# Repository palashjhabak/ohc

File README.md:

Open Home Control
=================

Open Home Control (OHC) is an **open source home automation system**
providing a framework for building up a bigger network of sensors and
actuators that all work together. It consists of several completely
developed hardware devices you can build up yourself and the software
running on those devices.

This project **concentrates on the hardware devices** and their software
(firmware), not on end user interfaces for control tasks like web
interfaces or smartphone apps. Nonetheless this system is designed to be
easily integrated in such systems.

For more information, visit the website at
http://www.open-home-control.com.

License Information Hardware Files
----------------------------------

All **hardware** files (schematics and layout) are stored under the
"hardware" subdirectory and are copyright (c) 2013 Uwe Freese, licensed
under the Creative Commons Attribution-ShareAlike 3.0 Unported:
(CC BY-SA 3.0): http://creativecommons.org/licenses/by-sa/3.0/deed.en.

License Information Software
----------------------------

All files not in the hardware subdirectory belong to the software (device
firmware or control software).

The Open Home Control **software** is free software: you can redistribute
it and/or modify it under the terms of the GNU General Public License as
published by the Free Software Foundation, either version 3 of the
License, or (at your option) any later version.

Open Home Control is distributed in the hope that it will be useful, but
WITHOUT ANY WARRANTY; without even the implied warranty of
MERCHANTABILITY or FITNESS FOR A PARTICULAR PURPOSE. See the GNU General
Public License for more details.

You should have received a copy of the GNU General Public License along
with Open Home Control. If not, see <http://www.gnu.org/licenses/>.

License Information Logo
------------------------

The Open Home Control logo ("House") and logotype, also used in the
hardware layouts, are copyrighted (c) by 2013 by Uwe Freese.

The logo and logotype may be used on hardware (boards or devices) or
description of those only for private purposes for devices included in
the project repository and which are therefore available to the public.
For derived or modified versions, devices not existing in the repository,
completely different products or for commercial boards or devices or to
describe them, the logo must not be used without explicit permission from
Uwe Freese.

For more information on using the logo or logotype outside the hardware
layouts, please read the legal info on the website
http://www.open-home-control.com.

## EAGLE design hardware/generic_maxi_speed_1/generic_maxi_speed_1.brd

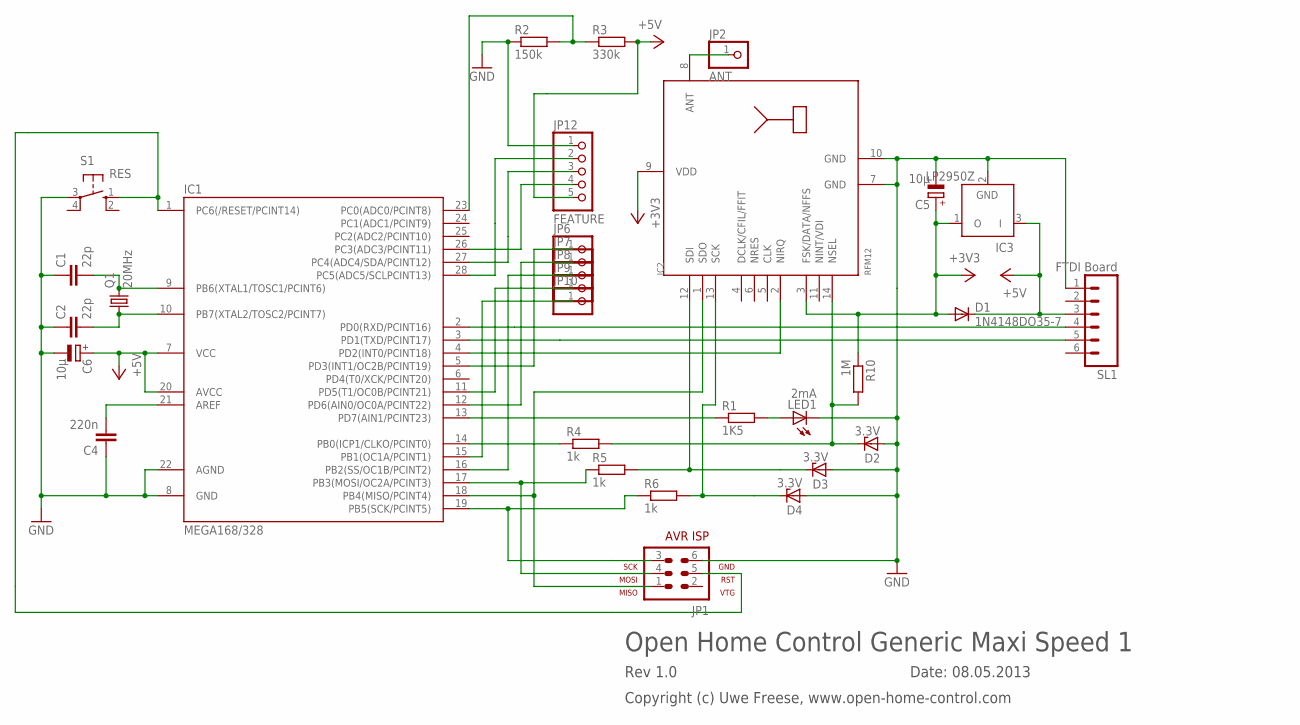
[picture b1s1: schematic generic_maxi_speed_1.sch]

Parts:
C1, C2: 22p; C025-024X044
C4: 220n; C025-030X050
C5, C6: 10µ; E1,8-4
D1: 1N4148DO35-7; DO35-7
D2, D3, D4: 3.3V; ZDIO-5
IC1: MEGA168/328; DIL28-3
IC2: RFM12; RFM
IC3: LP2950Z; TO92
JP1: AVR-ISP-6
JP2: ANT; 1X01
JP6, JP7, JP8, JP9, JP10: PINHD-1X1; 1X01
JP12: FEATURE; 1X05
LED1: 2mA; LED3MM
Q1: 20MHz; HC49/S
R1: 1K5; 0207/7
R2: 150k; 0207/7
R3: 330k; 0207/7
R4, R5, R6: 1k; 0207/7
R10: 1M; 0207/7
S1: RES; B3F-10XX
SL1: FTDI Board; 06P

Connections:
+3V3: C5.+, D1.A, IC2.3 (FSK/DATA/NFFS), IC2.9 (VDD), IC3.1 (O), R10.1
+5V: C6.+, D1.C, IC1.7 (VCC), IC1.20 (AVCC), IC3.3 (I), JP12.5, R3.2, SL1.3
GND: C1.1, C2.1, C4.1, C5.-, C6.-, D2.A, D3.A, D4.A, IC1.8 (GND), IC1.22 (AGND), IC2.7 (GND), IC2.10 (GND), IC3.2 (GND), JP1.6, JP12.1, LED1.K (C), R2.1, S1.3, SL1.1
unnamed: C1.2, IC1.9 (PB6(XTAL1/TOSC1/PCINT6)), Q1.2
unnamed: C2.2, IC1.10 (PB7(XTAL2/TOSC2/PCINT7)), Q1.1
unnamed: IC1.17 (PB3(MOSI/OC2A/PCINT3)), JP1.4, R5.1
unnamed: IC1.18 (PB4(MISO/PCINT4)), IC2.1 (SDO), JP1.1
unnamed: D4.C, IC2.13 (SCK), R6.2
unnamed: IC1.28 (PC5(ADC5/SCLPCINT13)), JP12.2
unnamed: IC1.19 (PB5(SCK/PCINT5)), JP1.3, R6.1
unnamed: IC1.1 (PC6(/RESET/PCINT14)), JP1.5, S1.1 (S)
unnamed: IC1.3 (PD1(TXD/PCINT17)), SL1.5
unnamed: IC1.2 (PD0(RXD/PCINT16)), SL1.4
unnamed: IC1.27 (PC4(ADC4/SDA/PCINT12)), JP12.3
unnamed: LED1.A, R1.2
unnamed: IC1.26 (PC3(ADC3/PCINT11)), JP12.4
unnamed: IC1.4 (PD2(INT0/PCINT18)), IC2.2 (NIRQ)
unnamed: D3.C, IC2.12 (SDI), R5.2
unnamed: IC1.5 (PD3(INT1/OC2B/PCINT19)), JP6.1
unnamed: IC1.23 (PC0(ADC0/PCINT8)), R2.2, R3.1
unnamed: IC1.11 (PD5(T1/OC0B/PCINT21)), JP9.1
unnamed: IC1.12 (PD6(AIN0/OC0A/PCINT22)), JP7.1
unnamed: IC1.13 (PD7(AIN1/PCINT23)), R1.1
unnamed: IC1.15 (PB1(OC1A/PCINT1)), JP10.1
unnamed: IC1.16 (PB2(SS/OC1B/PCINT2)), JP8.1
unnamed: C4.2, IC1.21 (AREF)
unnamed: IC2.8 (ANT), JP2.1
unnamed: IC1.14 (PB0(ICP1/CLKO/PCINT0)), R4.1
unnamed: D2.C, IC2.14 (NSEL), R4.2, R10.2

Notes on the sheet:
Open Home Control Generic Maxi Speed 1
Date: 08.05.2013
Rev 1.0
Copyright (c) Uwe Freese, www.open-home-control.com

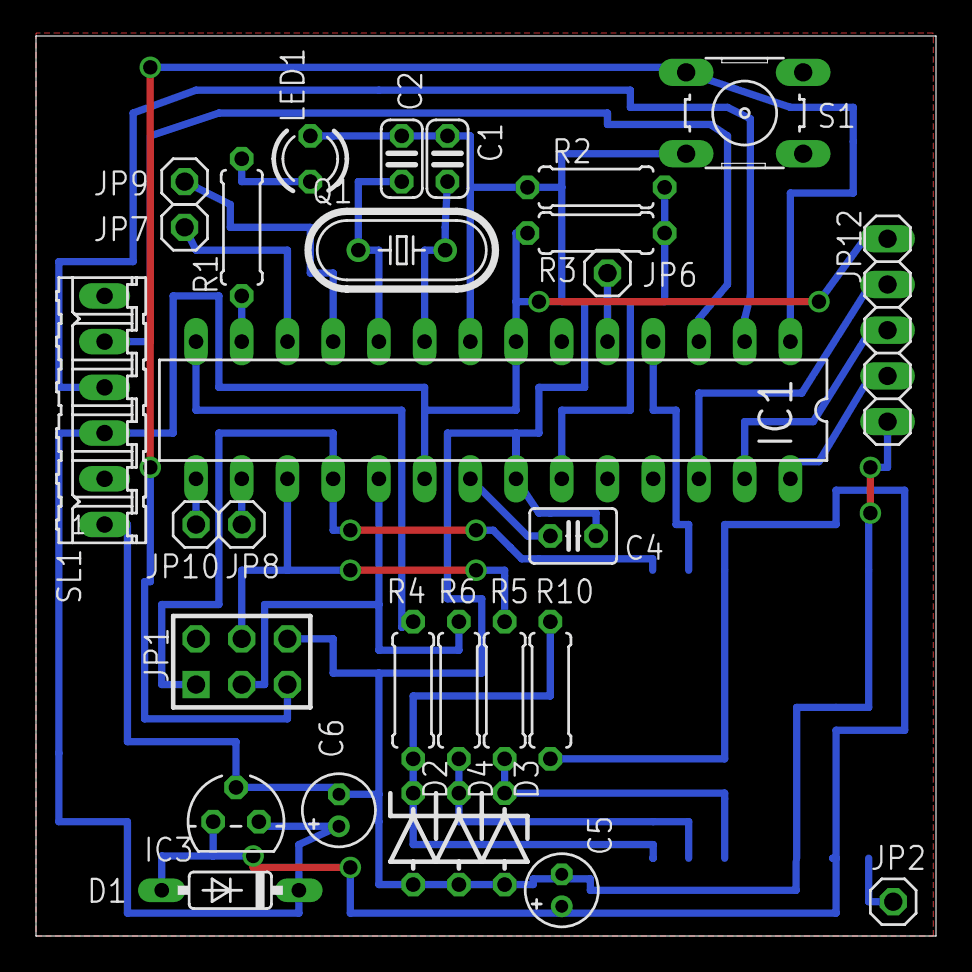
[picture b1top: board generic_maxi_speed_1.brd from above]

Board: 2 copper layers, 50.0 x 50.0 mm, 31 parts (1 on the bottom side), 29 nets.

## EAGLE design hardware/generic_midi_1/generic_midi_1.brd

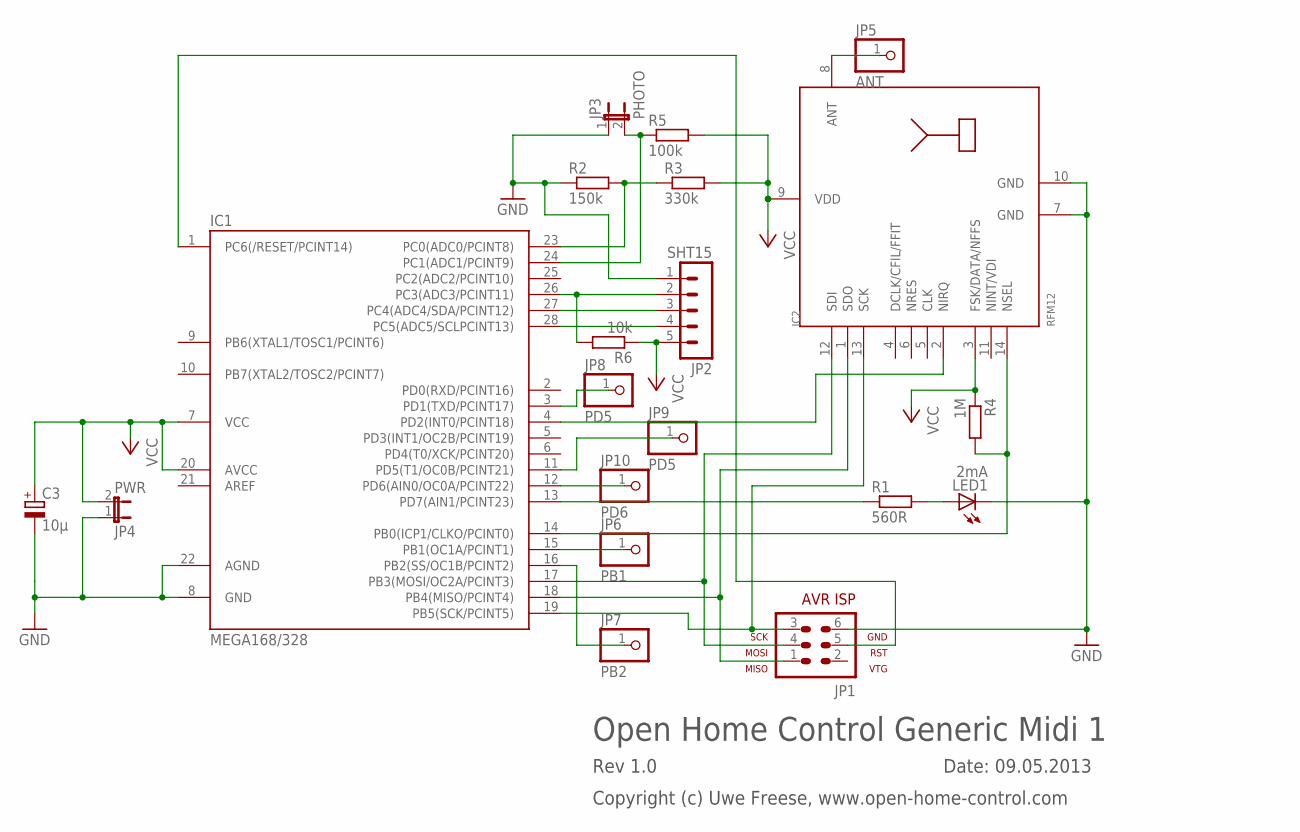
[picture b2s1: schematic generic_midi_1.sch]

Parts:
C3: 10µ; E1,8-4
IC1: MEGA168/328; DIL28-3
IC2: RFM12; RFM
JP1: AVR-ISP-6
JP2: SHT15; MA05-1
JP3: PHOTO; JP1
JP4: PWR; JP1
JP5: ANT; 1X01
JP6: PB1; 1X01
JP7: PB2; 1X01
JP8, JP9: PD5; 1X01
JP10: PD6; 1X01
LED1: 2mA; LED3MM
R1: 560R; 0207/7
R2: 150k; 0207/7
R3: 330k; 0207/7
R4: 1M; 0207/7
R5: 100k; 0207/7
R6: 10k; 0207/7

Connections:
GND: C3.-, IC1.8 (GND), IC1.22 (AGND), IC2.7 (GND), IC2.10 (GND), JP1.6, JP2.1, JP3.1, JP4.1, LED1.K (C), R2.1
unnamed: IC1.24 (PC1(ADC1/PCINT9)), JP3.2, R5.1
unnamed: IC1.17 (PB3(MOSI/OC2A/PCINT3)), IC2.12 (SDI), JP1.4
unnamed: IC1.18 (PB4(MISO/PCINT4)), IC2.1 (SDO), JP1.1
unnamed: IC1.19 (PB5(SCK/PCINT5)), IC2.13 (SCK), JP1.3
unnamed: IC1.13 (PD7(AIN1/PCINT23)), R1.1
unnamed: IC1.27 (PC4(ADC4/SDA/PCINT12)), JP2.3
unnamed: IC1.1 (PC6(/RESET/PCINT14)), JP1.5
unnamed: IC1.28 (PC5(ADC5/SCLPCINT13)), JP2.4
unnamed: IC1.26 (PC3(ADC3/PCINT11)), JP2.2, R6.2
unnamed: IC2.8 (ANT), JP5.1
unnamed: LED1.A, R1.2
unnamed: IC1.14 (PB0(ICP1/CLKO/PCINT0)), IC2.14 (NSEL), R4.2
unnamed: IC1.11 (PD5(T1/OC0B/PCINT21)), JP9.1
unnamed: IC1.4 (PD2(INT0/PCINT18)), IC2.2 (NIRQ)
unnamed: IC1.12 (PD6(AIN0/OC0A/PCINT22)), JP10.1
unnamed: IC1.15 (PB1(OC1A/PCINT1)), JP6.1
unnamed: IC1.23 (PC0(ADC0/PCINT8)), R2.2, R3.1
unnamed: IC1.16 (PB2(SS/OC1B/PCINT2)), JP7.1
unnamed: IC1.3 (PD1(TXD/PCINT17)), JP8.1
VCC: C3.+, IC1.7 (VCC), IC1.20 (AVCC), IC2.3 (FSK/DATA/NFFS), IC2.9 (VDD), JP2.5, JP4.2, R3.2, R4.1, R5.2, R6.1

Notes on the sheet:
Open Home Control Generic Midi 1
Date: 09.05.2013
Rev 1.0
Copyright (c) Uwe Freese, www.open-home-control.com

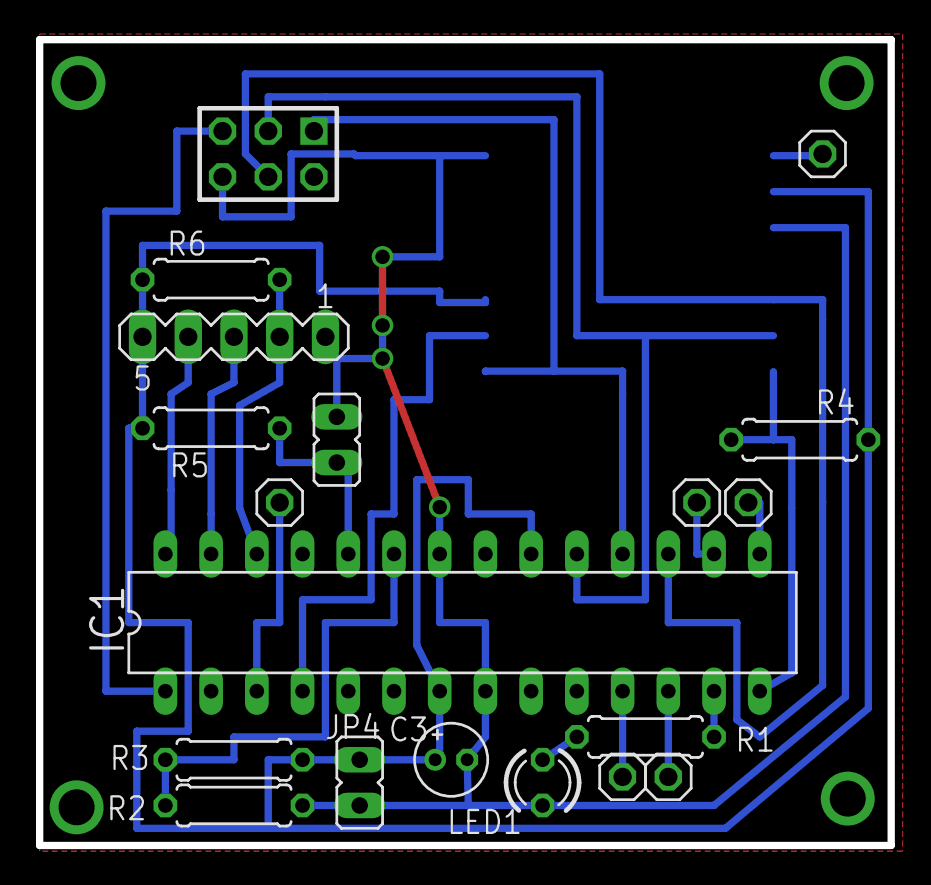
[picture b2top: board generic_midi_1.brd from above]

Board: 2 copper layers, 47.3 x 44.8 mm, 20 parts (1 on the bottom side), 21 nets.

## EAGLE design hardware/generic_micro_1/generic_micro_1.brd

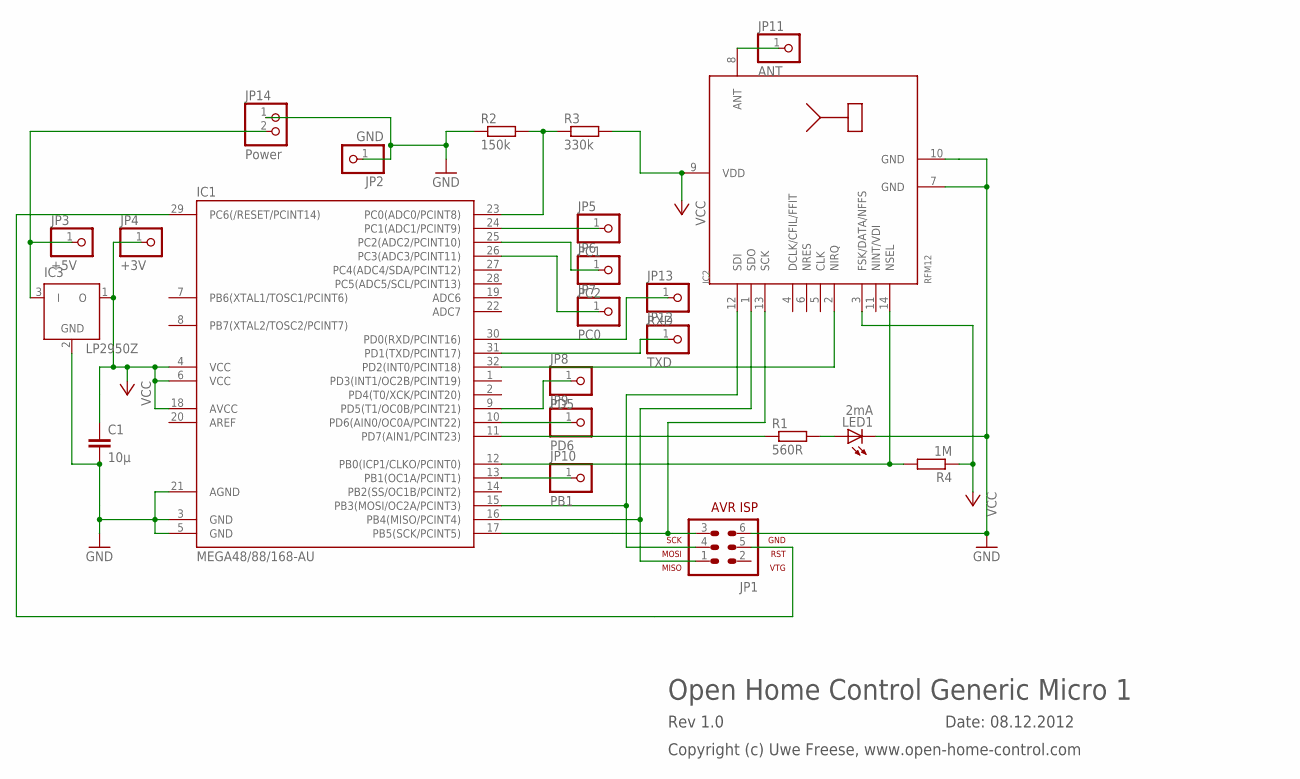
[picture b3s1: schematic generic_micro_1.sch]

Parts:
C1: 10µ; C0805
IC1: MEGA48/88/168-AU; TQFP32-08
IC2: RFM12; RFM
IC3: LP2950Z; TO92
JP1: AVR-ISP-6
JP2: GND; 1X01
JP3: +5V; 1X01
JP4: +3V; 1X01
JP5: PC1; 1X01
JP6: PC2; 1X01
JP7: PC0; 1X01
JP8: PD5; 1X01
JP9: PD6; 1X01
JP10: PB1; 1X01
JP11: ANT; 1X01
JP12: TXD; 1X01
JP13: RXD; 1X01
JP14: Power; 1X02
LED1: 2mA; LED3MM
R1: 560R; R0603
R2: 150k; R0603
R3: 330k; R0603
R4: 1M; R0603

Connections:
GND: C1.2, IC1.3 (GND), IC1.5 (GND), IC1.21 (AGND), IC2.7 (GND), IC2.10 (GND), IC3.2 (GND), JP1.6, JP2.1, JP14.1, LED1.K (C), R2.1
unnamed: IC1.26 (PC3(ADC3/PCINT11)), JP7.1
unnamed: IC1.24 (PC1(ADC1/PCINT9)), JP5.1
unnamed: IC1.15 (PB3(MOSI/OC2A/PCINT3)), IC2.12 (SDI), JP1.4
unnamed: IC1.16 (PB4(MISO/PCINT4)), IC2.1 (SDO), JP1.1
unnamed: IC1.17 (PB5(SCK/PCINT5)), IC2.13 (SCK), JP1.3
unnamed: IC1.11 (PD7(AIN1/PCINT23)), R1.1
unnamed: IC1.25 (PC2(ADC2/PCINT10)), JP6.1
unnamed: IC1.29 (PC6(/RESET/PCINT14)), JP1.5
unnamed: IC1.10 (PD6(AIN0/OC0A/PCINT22)), JP9.1
unnamed: IC1.9 (PD5(T1/OC0B/PCINT21)), JP8.1
unnamed: IC1.13 (PB1(OC1A/PCINT1)), JP10.1
unnamed: LED1.A, R1.2
unnamed: IC1.12 (PB0(ICP1/CLKO/PCINT0)), IC2.14 (NSEL), R4.2
unnamed: IC1.23 (PC0(ADC0/PCINT8)), R2.2, R3.1
unnamed: IC1.32 (PD2(INT0/PCINT18)), IC2.2 (NIRQ)
unnamed: IC2.8 (ANT), JP11.1
unnamed: IC3.3 (I), JP3.1, JP14.2
unnamed: IC1.31 (PD1(TXD/PCINT17)), JP12.1
unnamed: IC1.30 (PD0(RXD/PCINT16)), JP13.1
VCC: C1.1, IC1.4 (VCC), IC1.6 (VCC), IC1.18 (AVCC), IC2.3 (FSK/DATA/NFFS), IC2.9 (VDD), IC3.1 (O), JP4.1, R3.2, R4.1

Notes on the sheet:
Open Home Control Generic Micro 1
Date: 08.12.2012
Rev 1.0
Copyright (c) Uwe Freese, www.open-home-control.com

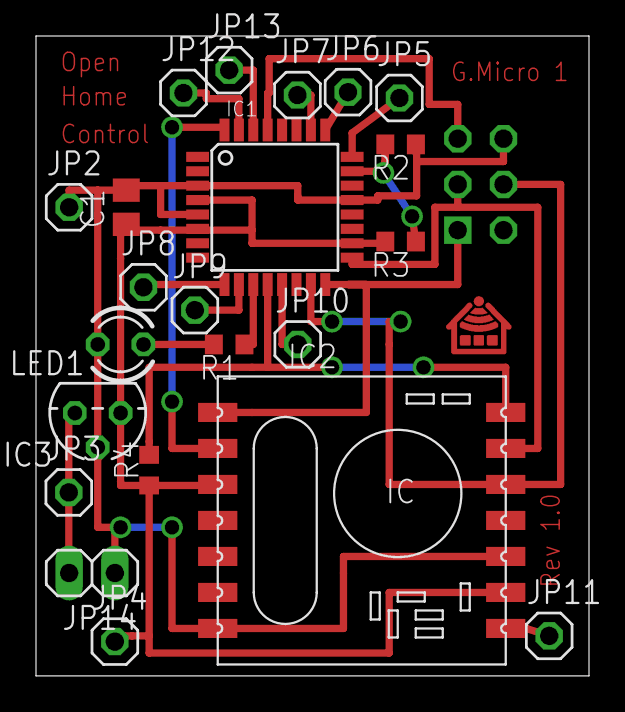
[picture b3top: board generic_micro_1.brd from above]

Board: 2 copper layers, 30.7 x 35.5 mm, 23 parts (1 on the bottom side), 21 nets.

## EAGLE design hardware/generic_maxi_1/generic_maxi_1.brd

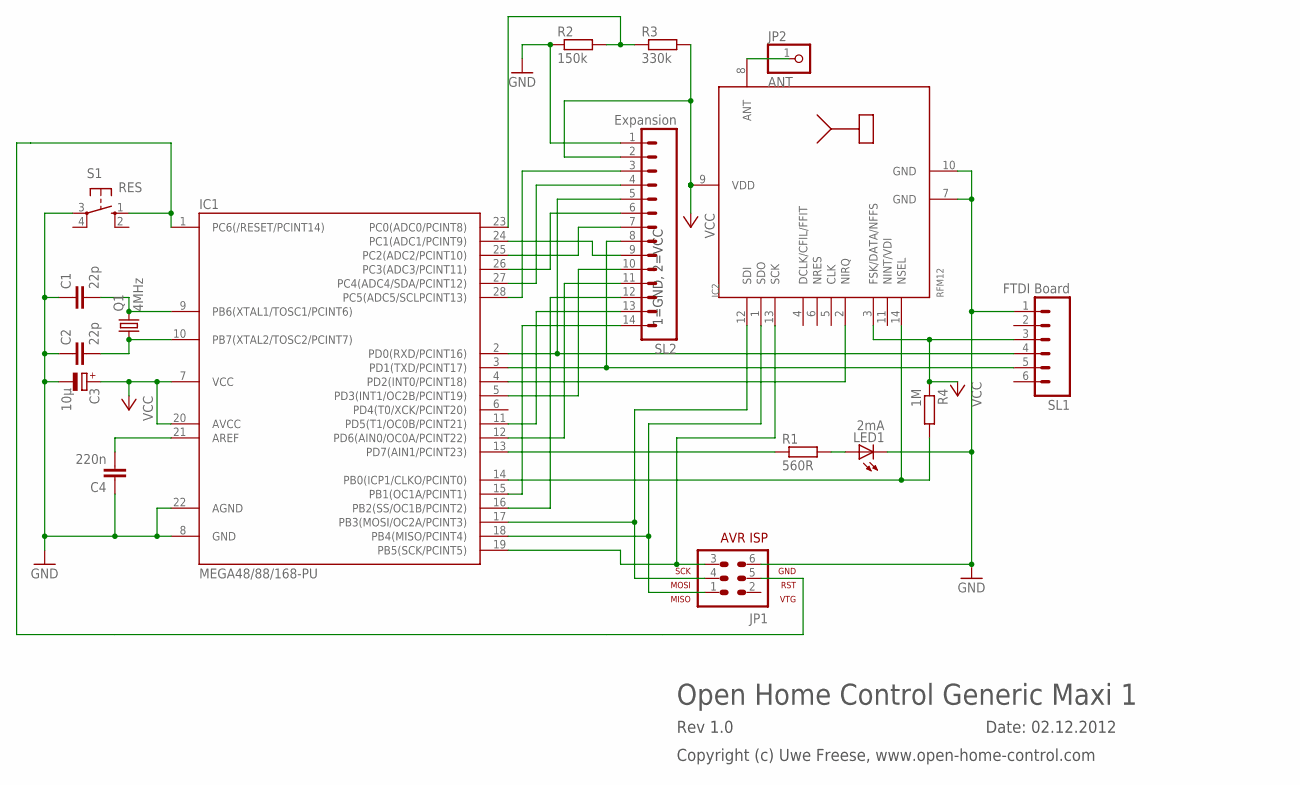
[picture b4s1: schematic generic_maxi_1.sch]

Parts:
C1, C2: 22p; C025-024X044
C3: 10µ; E1,8-4
C4: 220n; C025-030X050
IC1: MEGA48/88/168-PU; DIL28-3
IC2: RFM12; RFM
JP1: AVR-ISP-6
JP2: ANT; 1X01
LED1: 2mA; LED3MM
Q1: 4MHz; HC49/S
R1: 560R; 0207/7
R2: 150k; 0207/7
R3: 330k; 0207/7
R4: 1M; 0207/7
S1: RES; B3F-10XX
SL1: FTDI Board; 06P
SL2: Expansion; 14P

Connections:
GND: C1.1, C2.1, C3.-, C4.1, IC1.8 (GND), IC1.22 (AGND), IC2.7 (GND), IC2.10 (GND), JP1.6, LED1.K (C), R2.1, S1.3, SL1.1, SL2.1
unnamed: C1.2, IC1.9 (PB6(XTAL1/TOSC1/PCINT6)), Q1.2
unnamed: C2.2, IC1.10 (PB7(XTAL2/TOSC2/PCINT7)), Q1.1
unnamed: IC1.17 (PB3(MOSI/OC2A/PCINT3)), IC2.12 (SDI), JP1.4
unnamed: IC1.18 (PB4(MISO/PCINT4)), IC2.1 (SDO), JP1.1
unnamed: IC1.19 (PB5(SCK/PCINT5)), IC2.13 (SCK), JP1.3
unnamed: IC1.27 (PC4(ADC4/SDA/PCINT12)), SL2.4
unnamed: IC1.28 (PC5(ADC5/SCLPCINT13)), SL2.3
unnamed: IC1.1 (PC6(/RESET/PCINT14)), JP1.5, S1.1 (S)
unnamed: IC1.3 (PD1(TXD/PCINT17)), SL1.5, SL2.8
unnamed: IC1.2 (PD0(RXD/PCINT16)), SL1.4, SL2.5
unnamed: IC1.24 (PC1(ADC1/PCINT9)), SL2.9
unnamed: LED1.A, R1.2
unnamed: IC1.14 (PB0(ICP1/CLKO/PCINT0)), IC2.14 (NSEL), R4.2
unnamed: IC1.25 (PC2(ADC2/PCINT10)), SL2.7
unnamed: IC1.4 (PD2(INT0/PCINT18)), IC2.2 (NIRQ)
unnamed: IC1.26 (PC3(ADC3/PCINT11)), SL2.6
unnamed: IC1.5 (PD3(INT1/OC2B/PCINT19)), SL2.10
unnamed: IC1.23 (PC0(ADC0/PCINT8)), R2.2, R3.1
unnamed: IC1.11 (PD5(T1/OC0B/PCINT21)), SL2.13
unnamed: IC1.12 (PD6(AIN0/OC0A/PCINT22)), SL2.11
unnamed: IC1.13 (PD7(AIN1/PCINT23)), R1.1
unnamed: IC1.15 (PB1(OC1A/PCINT1)), SL2.14
unnamed: IC1.16 (PB2(SS/OC1B/PCINT2)), SL2.12
unnamed: C4.2, IC1.21 (AREF)
unnamed: IC2.8 (ANT), JP2.1
VCC: C3.+, IC1.7 (VCC), IC1.20 (AVCC), IC2.3 (FSK/DATA/NFFS), IC2.9 (VDD), R3.2, R4.1, SL1.3, SL2.2

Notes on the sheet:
1=GND, 2=VCC
Open Home Control Generic Maxi 1
Date: 02.12.2012
Rev 1.0
Copyright (c) Uwe Freese, www.open-home-control.com

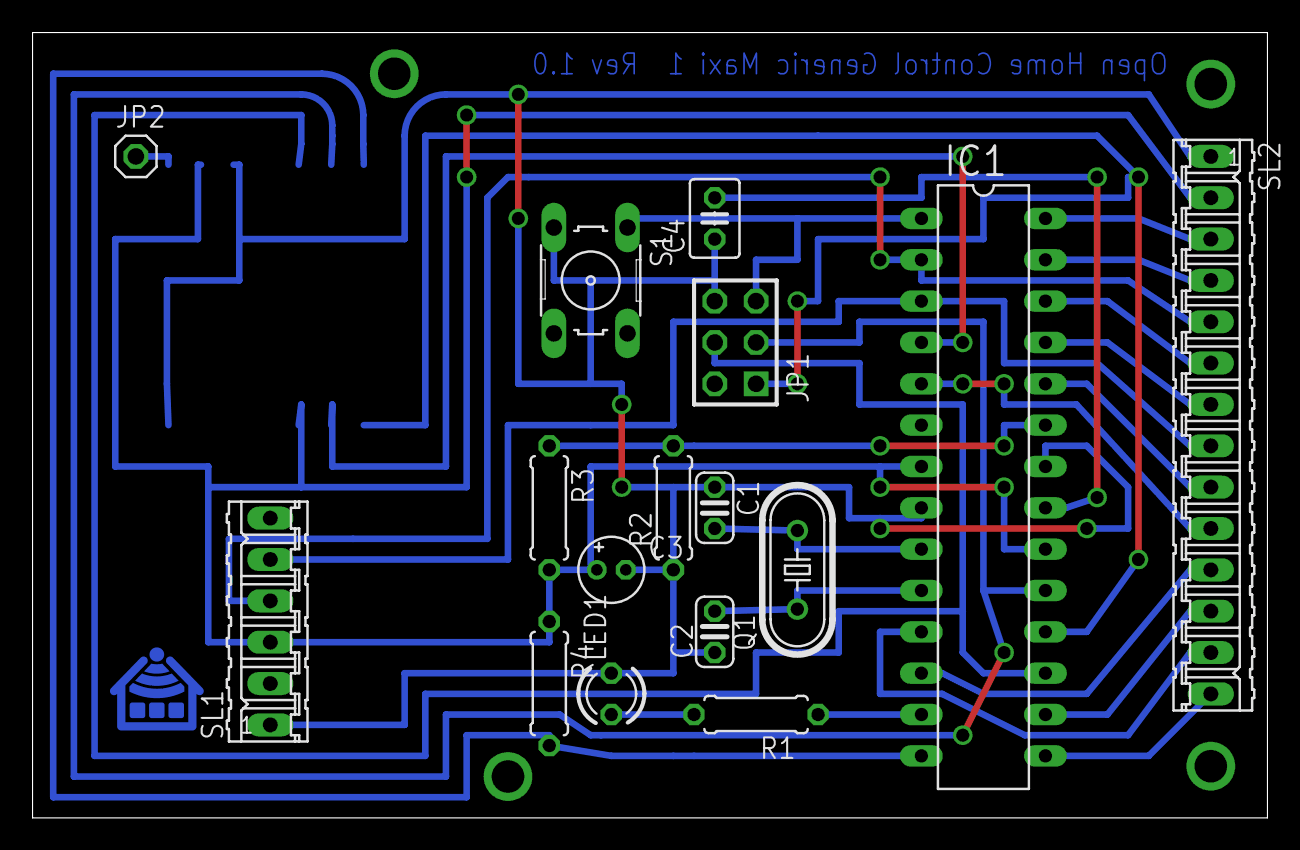
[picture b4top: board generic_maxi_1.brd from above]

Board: 2 copper layers, 75.9 x 48.2 mm, 17 parts (1 on the bottom side), 27 nets.

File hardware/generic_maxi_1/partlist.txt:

Partlist

Exported from generic_maxi_1.sch at 05.11.2012 21:27:49

EAGLE Version 6.2.0 Copyright (c) 1988-2012 CadSoft

Assembly variant: 

Part     Value            Device           Package      Library       Sheet

C1       22p              C-EU025-024X044  C025-024X044 rcl           1
C2       22p              C-EU025-024X044  C025-024X044 rcl           1
C3       10µ              CPOL-EUE1.8-4    E1,8-4       rcl           1
C4       220n             C-EU025-030X050  C025-030X050 rcl           1
IC1      MEGA48/88/168-PU MEGA48/88/168-PU DIL28-3      avr-5-4.16    1
IC2      RFM12            RFM12            RFM          hopeRF        1
JP1      AVR-ISP-6        AVR-ISP-6        AVR-ISP-6    avr-5-4.16    1
JP2      ANT              PINHD-1X1        1X01         pinhead       1
LED1     2mA              LED3MM           LED3MM       led           1
Q1       4MHz             CRYSTALHC49S     HC49/S       crystal       1
R1       750R             R-EU_0207/7      0207/7       rcl           1
R2       150k             R-EU_0207/7      0207/7       rcl           1
R3       330k             R-EU_0207/7      0207/7       rcl           1
R4       1M               R-EU_0207/7      0207/7       rcl           1
S1       RES              10-XX            B3F-10XX     switch-omron  1
SL1      FTDI Board       M06              06P          con-amp-quick 1
SL2      Expansion        M14              14P          con-amp-quick 1

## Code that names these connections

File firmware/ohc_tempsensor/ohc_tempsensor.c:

/*
* This file is part of Open Home Control, http://www.open-home-control.com.
* Copyright (c) 2013 Uwe Freese
*
* Open Home Control is free software: you can redistribute it and/or modify
* it under the terms of the GNU General Public License as published by the
* Free Software Foundation, either version 3 of the License, or (at your
* option) any later version.
*
* Open Home Control is distributed in the hope that it will be useful, but
* WITHOUT ANY WARRANTY; without even the implied warranty of
* MERCHANTABILITY or FITNESS FOR A PARTICULAR PURPOSE. See the GNU General
* Public License for more details.
*
* You should have received a copy of the GNU General Public License along
* with Open Home Control. If not, see <http://www.gnu.org/licenses/>.
*/

#include <avr/io.h>
#include <avr/interrupt.h>
#include <util/delay.h>
#include <string.h>
#include <avr/wdt.h>
#include <avr/sleep.h>
#include <avr/eeprom.h>

#include "rfm12.h"
#include "uart.h"

// switch on debugging by UART
//#define UART_DEBUG

// switch on voltage check of battery on PC0 (ADC0)
#define VBAT_SENSOR

// switch on SHT15 temperature / humidity sensor on PC2 + PC3
#define TEMP_SENS

// switch on light sensor on PC1 (ADC1)
#define LIGHT_SENS

#ifdef TEMP_SENS
	#include "sht11.h"
#endif

#include "../src_common/aes256.h"
#include "util.h"

#define AVERAGE_COUNT 4 // Average over how many values before sending over RFM12?

#define EEPROM_POS_DEVICE_ID 8
#define EEPROM_POS_PACKET_COUNTER 9
#define EEPROM_POS_AES_KEY 32

// How often should the packetcounter_base be increased and written to EEPROM?
// This should be 2^32 (which is the maximum transmitted packet counter) /
// 100.000 (which is the maximum amount of possible EEPROM write cycles) or more.
// Therefore 100 is a good value.
#define PACKET_COUNTER_WRITE_CYCLE 100

uint32_t packetcounter = 0;

void printbytearray(uint8_t * b, uint8_t len)
{
	uint8_t i;
	
	for (i = 0; i < len; i++)
	{
		UART_PUTF("%02x ", b[i]);
	}
	
	UART_PUTS ("\r\n");
}

void rfm12_sendbuf(void)
{
	#ifdef UART_DEBUG
	UART_PUTS("Before encryption: ");
	printbytearray(bufx, 16);
	#endif

	uint8_t aes_byte_count = aes256_encrypt_cbc(bufx, 16);

	#ifdef UART_DEBUG
	UART_PUTS("After encryption:  ");
	printbytearray(bufx, aes_byte_count);
	#endif

	rfm12_tx(aes_byte_count, 0, (uint8_t *) bufx);
}

int main ( void )
{
	uint16_t vbat = 0;
	uint16_t vlight = 0;
	int16_t temp = 0;
	uint16_t hum = 0;
	uint8_t device_id = 0;
	uint8_t avg = 0;

	// delay 1s to avoid further communication with uart or RFM12 when my programmer resets the MC after 500ms...
	_delay_ms(1000);

	util_init();

	// read packetcounter, increase by cycle and write back
	packetcounter = eeprom_read_dword((uint32_t*)EEPROM_POS_PACKET_COUNTER) + PACKET_COUNTER_WRITE_CYCLE;
	eeprom_write_dword((uint32_t*)0, packetcounter);

	// read device id and write to send buffer
	device_id = eeprom_read_byte((uint8_t*)EEPROM_POS_DEVICE_ID);	
	
	//osccal_init();
	
#ifdef UART_DEBUG
	uart_init();
	UART_PUTS ("\r\n");
	UART_PUTS ("RFM12 Transmitter V1.0 (c) Uwe Freese, www.uwe-freese.de\r\n");
	UART_PUTF ("Device ID: %u\r\n", device_id);
	UART_PUTF ("Packet counter: %u\r\n", packetcounter);
#endif
	
	// init AES key
	eeprom_read_block (aes_key, (uint8_t *)EEPROM_POS_AES_KEY, 32);

#ifdef VBAT_SENSOR
	adc_init();
#endif

#ifdef TEMP_SENS
	sht11_init();
#endif

	rfm12_init();
	//rfm12_set_wakeup_timer(0b11100110000);   // ~ 6s
	//rfm12_set_wakeup_timer(0b11111000000);   // ~ 24576ms
	//rfm12_set_wakeup_timer(0b0100101110101); // ~ 59904ms
	rfm12_set_wakeup_timer(0b101001100111); // ~ 105472ms  CORRECT VALUE!!!

	led_blink(100, 150, 20);

	sei();

	while (42)
	{
#if defined VBAT_SENSOR || defined LIGHT_SENS
		adc_on(true);
#endif

#ifdef VBAT_SENSOR
		vbat += (int)((long)read_adc(0) * 34375 / 10000 / 2); // 1.1 * 480 Ohm / 150 Ohm / 1,024
#endif

#ifdef LIGHT_SENS
		vlight += read_adc(1);
#endif

#if defined VBAT_SENSOR || defined LIGHT_SENS
		adc_on(false);
#endif

#ifdef TEMP_SENS
		sht11_start_measure();
		_delay_ms(500);
		while (!sht11_measure_finish());
		
		temp += sht11_get_tmp();
		hum += sht11_get_hum();
#endif

		avg++;
		
		if (avg >= AVERAGE_COUNT)
		{
			vbat /= AVERAGE_COUNT;
			vlight /= AVERAGE_COUNT;
			temp /= AVERAGE_COUNT;
			hum /= AVERAGE_COUNT;

			// set device ID
			bufx[0] = device_id;
			
			// update packet counter
			packetcounter++;
			
			if (packetcounter % PACKET_COUNTER_WRITE_CYCLE == 0)
			{
				eeprom_write_dword((uint32_t*)0, packetcounter);
			}

			setBuf32(1, packetcounter);

			// set command ID 10 (Temperature Sensor Status)
			bufx[5] = 10;

			// update battery percentage
			bufx[6] = bat_percentage(vbat);

			// update temperature and humidity
#ifdef TEMP_SENS
			setBuf16(7, (uint16_t)temp);
			setBuf16(9, hum);
#endif

			// update brightness
#ifdef LIGHT_SENS
			bufx[11] = 100 - (int)((long)vlight * 100 / 1024);
#endif
			uint32_t crc = crc32(bufx, 12);
			UART_PUTF("CRC32 is %lx (added as last 4 bytes)\r\n", crc);
			setBuf32(12, crc);

#ifdef UART_DEBUG
//			UART_PUTF3("Battery: %u%%, Temperature: %d deg.C, Humidity: %d%%\r\n", bat_percentage(vbat), temp / 100.0, hum / 100.0);
#endif

			rfm12_sendbuf();
			
			rfm12_tick(); // send packet, and then WAIT SOME TIME BEFORE GOING TO SLEEP (otherwise packet would not be sent)

			switch_led(1);
			_delay_ms(200);
			switch_led(0);

			vbat = temp = hum = vlight = avg = 0;
		}
		
		// go to sleep. Wakeup by RFM12 wakeup-interrupt
		set_sleep_mode(SLEEP_MODE_PWR_DOWN);
        sleep_mode();
	}
}

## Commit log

2013-04-14 add initial files
2013-04-15 correct license info
2013-04-20 update license info
2013-04-28 add dual voltage PCB for base station
2013-04-29 Add generic midi 2.
2013-04-30 add generic maxi speed layout
2013-05-01 Moved capacitor near to RFM12. Added zener diodes instead of resistors. Avoid one bridge connection.
2013-05-01 Remove generic midi 2, which was just an idea. Better use the Generic maxi speed for the base station.
2013-05-01 change drill size of via
2013-05-01 Improved distance between some pcb tracks.
2013-05-02 Rev 1.0 finished, circuit working. Add mask and placing picture.
2013-05-02 Use 20 MHz external crystal for base station. Use Generic Maxi Speed to support this.
2013-05-08 Changed microcontroller name to MEGA168/328
2013-05-08 optimized label positions. Rename ATMega model in label.
2013-05-09 renames connectors, changed positions of labels, updated mask, placing and partlist
2013-05-09 moved some labels, updated picture
2013-05-12 make encryption test code working again (if commented in)
